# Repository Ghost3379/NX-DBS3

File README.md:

# NX-Edge

> **High-Density Modular Embedded Development Platform**  
> *M.2 2280 Key B • 6-Layer High-Density RF/Power Stackup • ESP32-S3 Dual-Core 240MHz • Autonomous LiPo Power-Path & Fuel Gauge • Dual-Antenna RF Front-End • Switched NeoPixel Driver*

---

<p align="center">
  <em>NX-Edge 3D Render — Dense 6-layer layout in M.2 2280 Key B form factor featuring 45° ESP32-S3, WSON-8 Flash, Ignion Chip Antenna + U.FL, LiPo Charger, Fuel Gauge, 2A Buck Regulator, and Switched NeoPixel Bus.</em>
</p>

---

## Overview

The **NX-Edge** is an ultra-dense, agile embedded development platform engineered to bridge the gap between high-speed benchtop prototyping and space-constrained, high-vibration interactive builds (tactical gear, robotics, custom sabers, wearable tech, and modular IoT nodes).

Built in the standard **M.2 2280 ($22 \times 80\text{ mm}$)** envelope on an advanced **6-layer high-density PCB** with **100% single-sided component placement** (zero components on the bottom layer), the NX-Edge delivers a **hybrid mechanical and electrical architecture**:

1. **The Modular Cartridge:** Standard **M.2 Key B edge connector** (up to 75 pins) allowing the board to slide directly into low-profile carrier boards, custom backplanes, or modular hilt sleds.
2. **The Castellated Prototyping Companion:** Dual perimeter rows of **castellated edge holes and solder pads** allow the board to be used directly on breadboards with pin headers, wired via fly-leads, or soldered flat as a surface-mount System-on-Module (SoM) onto carrier PCBs without requiring an M.2 socket.
3. **Zero-Z Flat Bottom:** Because all active ICs, passives, and connectors are strictly top-mounted, the bottom is flat copper and solder mask—allowing it to be mounted flush against aluminum chassis, heatsinks, 3D prints, or battery packs using thermal tape without risk of short circuits.

> [!IMPORTANT]
> **NX Custom Maker Interconnect (Non-PC Hardware):**  
> While the board utilizes the standard mechanical **M.2 Key B form factor and connector**, the pinout is a **custom, high-power maker standard** (similar to SparkFun MicroMod). The M.2 connector routes raw battery power, high-current 5V rails, speaker outputs, and 3.3V GPIOs directly to custom carrier boards. **Do NOT plug this board into a standard PC motherboard M.2 NVMe/SATA slot.**

---

## Current Hardware Implementation Status

| Subsystem / Block | Status | Key Components & Implementation Details |
| :--- | :---: | :--- |
| **Compute Core** | **Routed** | ESP32-S3 (bare QFN-56 @ 45°), 40 MHz 2016 crystal with symmetrical wings, decoupling network on power rails. |
| **Flash Memory** | **Routed** | 16 MB Winbond `W25Q128JVPIQ` (WSON-8), inline decoupling, Quad-SPI bus routed on internal Layer 3 stripline. |
| **RF Front-End** | **Routed** | Ignion `NN02-201` ceramic antenna + Hirose U.FL receptacle + Infineon `BGS12WN6` SPDT RF switch (`RF_CTRL`). |
| **USB Type-C** | **Routed** | Reversible Type-C receptacle, `USBLC6-2SC6` ESD array, dual $5.1\,\text{k}\Omega$ CC pulldowns (`R20`/`R21`), D+/D- internal stripline. |
| **LiPo Charging** | **Routed** | TI `BQ25170` autonomous linear charger (600–800 mA), status LED, horizontal JST-PH 2.0mm connector (`P1`/`P2`). |
| **True 0µA Standby** | **Routed** | Solder jumper & switch pad `JP2` between battery and system rail for an external physical power switch. |
| **Buck Regulator** | **Routed** | TI `TLV62569` synchronous buck converter delivering continuous **3.3V @ 2.0A** with low ripple. |
| **Fuel Gauge** | **Routed** | Maxim `MAX17048` ModelGauge™ I2C fuel gauge (`0x36`) for cell voltage ($V_{CELL}$) and SoC% without IR drop. |
| **NeoPixel Driver** | **Routed** | P-FET `Q2` (DMP3130L-7) + NPN `Q3` (BC847W) on `IO12` with 3 castellated pads (`VN`, `NPD_IN`, `GND`) for high-power strips. |
| **Onboard Indicators**| **Routed** | Onboard RGB NeoPixel (WS2812B/SK6812) powered from `VN` + User LED (LED13 / `D3`) with resistor `R13`. |
| **6-Layer Stackup** | **Configured**| Upgraded from 4-layer to high-density 6-layer with 0.45 mm / 0.25 mm micro-vias for optimal signal integrity. |
| **MicroSD Slot** | *Planned* | Molex 105162 push-pull slot running in native **4-bit hardware SDMMC** mode via ESP32-S3 DMA engine. |
| **Motion Sensor** | *Planned* | CEVA / Hillcrest Labs `BNO085` 9-DOF IMU with dedicated 32.768 kHz quartz crystal and sensor-fusion engine. |
| **Audio Amplifier** | *Planned* | Maxim `MAX98357A` I2S Class-D mono amplifier delivering up to 3.2W into 4Ω directly from `VIN`. |
| **RTC Subsystem** | *Planned* | Micro Crystal `RV-3028-C7` extreme low-power ($45\,\text{nA}$) real-time clock with backup cap `C34`. |

---

## 6-Layer High-Density Stackup Architecture

To ensure pristine signal integrity, zero electromagnetic interference (EMI) between the 2.4 GHz RF stage and high-speed digital buses, and effortless escape routing for QFN/WSON packages, the NX-Edge employs an industrial **6-layer symmetrical stackup**:

| Layer | KiCad Layer | Type | Copper Role & Signal Integrity Function |
| :---: | :---: | :---: | :--- |
| **L1** | `F.Cu` | Mixed / Top | Component mounting, 2.4 GHz RF transmission line, localized power pours (`VIN`, `+3V3`, `VBAT`). |
| **L2** | `In1.Cu` | Plane | **Solid Ground Plane (GND):** Uninterrupted return path and Faraday shield directly below Top layer. |
| **L3** | `In2.Cu` | Stripline Sig | **High-Speed Signal Highway:** Fully shielded internal striplines for **USB D+/D-**, **Flash Quad-SPI**, and **SDMMC**. |
| **L4** | `In3.Cu` | Power Plane | **Power Plane Mosaic:** Low-impedance internal distribution for `+3V3`, `VBUS`, and `VBAT`. |
| **L5** | `In4.Cu` | Plane | **Secondary Solid Ground Plane (GND):** Complete ground shield referencing Bottom layer. |
| **L6** | `B.Cu` | Mixed / Bottom | Non-critical escape routing, switched `VN` power plane, M.2 docking fingers, and edge test pads. |

* **Via Geometry:** Optimized to **0.45 mm pad diameter / 0.25 mm drill hole** (0.1 mm annular ring), shrinking via area by ~45% compared to standard 0.6/0.3 mm vias and allowing traces to slip between pins without DRC bottlenecks.

---

## Power Architecture & Power-Path Topology

The NX-Edge implements an autonomous, low-loss **Power-Path management architecture**:

```text
  USB-C (VBUS 5V) ──► [Schottky D2] ─────────┐
                                              │
  LiPo (VBAT) ────► [Hard-Cut JP2] ──► [Q1] ──┴─► [ VIN ] (Automatic System Rail)
                                        ▲           │
                                        │ Gate      ├─► [TLV62569 Buck] ──► +3V3 (2.0A)
                                  (VBUS Controlled) │
                                                    ├─► [MAX17048 Gauge] (I2C SoC Monitoring)
                                                    │
                                                    └─► [Q2 P-FET / Q3 NPN] ──► VN (Switched NeoPixel Rail)
                                                              ▲
                                                              │ GPIO12 (CTRL_NP)
```

1. **Automatic Power-Path Node (`VIN`):**
   * Sourced through Schottky diode from USB `VBUS` ($5.0\text{V}$) or low-loss P-MOSFET from battery `VBAT` ($3.7\text{–}4.2\text{V}$).
   * **USB Connected:** `VBUS` holds the P-FET gate high, completely isolating the battery from system discharge. `VIN` runs directly on USB power ($\approx 4.8\text{–}5.0\text{V}$).
   * **Battery Only:** When USB is disconnected, a gate pull-down immediately engages the P-FET ($R_{DS(on)} \approx 30\text{ m}\Omega$), supplying `VIN` with virtually zero voltage drop.
2. **System Buck Regulator (`TLV62569`):**
   * Synchronous step-down buck converter delivering **$3.3\text{V} @ \mathbf{2.0\text{A}}$ continuous** with $>95\%$ efficiency.
   * Powers the ESP32-S3, Flash, sensors, and peripherals cleanly without thermal throttling.
3. **Autonomous LiPo Charger (`BQ25170`):**
   * Standalone linear charger powered from `VBUS` configured for $600\text{–}800\text{ mA}$ charging with NTC thermistor input.
   * **Decoupled Charging:** Because the system and external LEDs run from `VIN`, charging current is never hijacked by system load.
4. **ModelGauge™ Fuel Gauge (`MAX17048`):**
   * Precision I2C fuel gauge (`0x36`) monitoring cell voltage directly at the battery connector. Reports cell voltage ($V_{CELL}$ in mV), State of Charge (SOC %), and rate of change over I2C without burning ADC channels or suffering from trace IR-drop.
5. **Smart NeoPixel Power-Cut (`VN`):**
   * High-side P-MOSFET `Q2` driven by NPN BJT `Q3` controlled via **GPIO12 (`CTRL_NP`)**.
   * In Standby/Deep Sleep (`CTRL_NP = LOW`), power to both onboard and external NeoPixels is cut to $0.0\text{V}$, eliminating the $\sim 1\text{ mA}$ per-pixel quiescent vampire draw ($0.0\,\mu\text{A}$ standby).

---

## RF Agility & Dual-Antenna Switching

* **RF Switch:** Infineon **`BGS12WN6`** ultra-miniature ($0.7 \times 1.1\text{ mm}$) SPDT RF switch rated up to $6\text{ GHz}$ with $<0.3\text{ dB}$ insertion loss.
* **Control:** Controlled via **`RF_CTRL`**:
  * **Low (Default):** On-board high-efficiency **Ignion NN02-201** ceramic chip antenna.
  * **High:** Micro-coaxial **Hirose U.FL / IPEX** receptacle for external antenna routing out of metal, carbon fiber, or shielded enclosures.

---

## Mechanical Specifications

* **Form Factor Standard:** M.2 2280 ($22.0\text{ mm} \times 80.0\text{ mm}$).
* **Connector Type:** M.2 Key B card edge (up to 75 pins).
* **PCB Thickness:** Standard $1.6\text{ mm}$ (or $0.8\text{ mm}$ option for slimline M.2 sockets).
* **Component Clearance:** 100% single-sided top placement. Completely flat bottom surface.
* **Prototyping Headers:** Dual-edge castellated pin holes for breadboards and surface mounting.

---

## License & Ownership

* **Hardware Design:** Licensed under the [CERN Open Hardware Licence Version 2 - Strongly Reciprocal (CERN-OHL-S)](https://ohwr.org/cernohl).
* **Firmware / BSP:** Licensed under the [GNU General Public License v3.0 (GPLv3)](https://www.gnu.org/licenses/gpl-3.0.en.html).
* **Engineering & Ownership:** Conceptualized, engineered, and maintained by [@Ghost3379](https://github.com/Ghost3379).

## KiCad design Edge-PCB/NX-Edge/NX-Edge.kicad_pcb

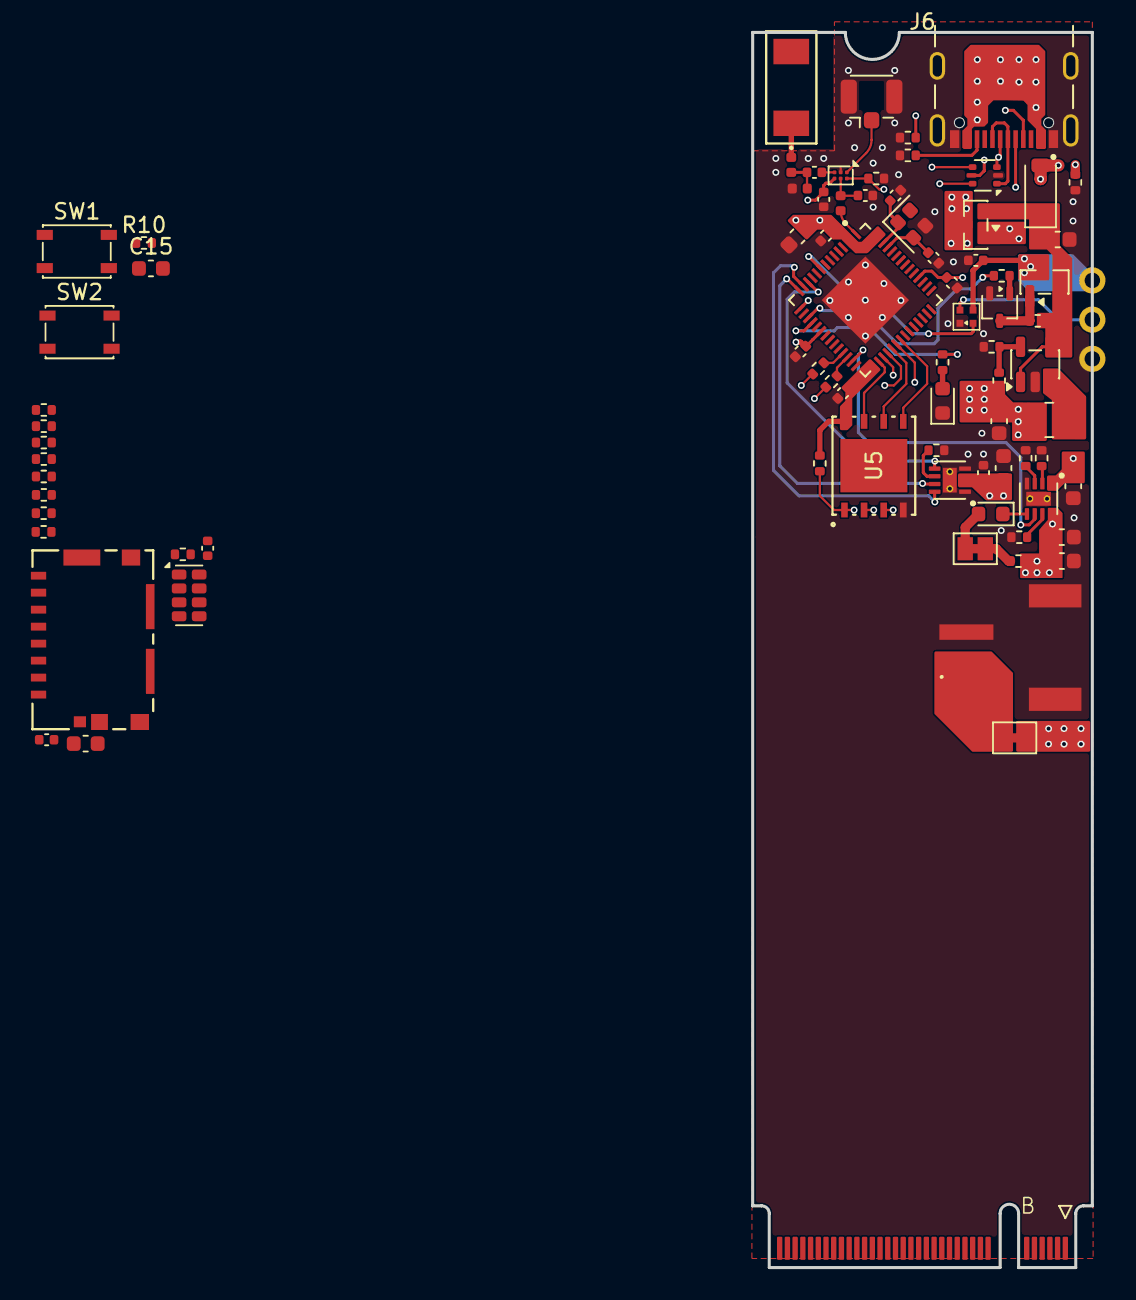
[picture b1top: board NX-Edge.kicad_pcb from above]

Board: 6 copper layers, 22.0 x 80.0 mm, 80 parts (0 on the bottom side), 64 nets.

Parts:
AE1: NN02-201; ANT_NN02-201_IGN
AE2: U-FL Connector; U.FL_Hirose_U.FL-R-SMT-1_Vertical
C1, C2, C15, C22: 1u; C_0603_1608Metric
C3, C5, C7, C20: 10u; C_0603_1608Metric
C4: 4.7u; C_0603_1608Metric
C6, C8, C11, C12, C16, C19, C21, C23, C24: 100n; C_0402_1005Metric
C13, C14: TBA; C_0402_1005Metric
C17, C18: 12p; C_0402_1005Metric
D1: ORANGE; LED_0603_1608Metric
D2: NRVB230LSFT1G; D_SOD-123
D3: BLUE; LED_0603_1608Metric
J1: 1051620001; 105162-0001_MOL
J3: UJ20-C-H-G-SMT-1-P16-TR; SAMESKY_UJ20-C-H-G-SMT-1-P16-TR
J6: Bus_M.2_Socket_B; M.2_2280-xx-B
J7: Ext. NeoPixel; PinHeader_1x03_P2.54mm_Vertical
JP1: CUT2DISABLE; SolderJumper-2_P1.3mm_Bridged_Pad1.0x1.5mm
JP2: PLACE4SWITCH; SolderJumper-2_P1.3mm_Bridged_Pad1.0x1.5mm
L1: 1u; L_1008_2520Metric
L2, L3, L4: TBA; L_0402_1005Metric
P1: S2B-PH-SM4-TB; JST_S2B-PH-SM4-TB
Q1, Q2: DMP3130L-7; SOT-23
Q3: BC847W; SOT-323_SC-70
R1, R8, R13: 1k; R_0402_1005Metric
R2: 27k; R_0402_1005Metric
R3: 499; R_0402_1005Metric
R4: 453k; R_0402_1005Metric
R5, R6, R9, R11: 100k; R_0402_1005Metric
R7, R14: 10k; R_0402_1005Metric
R10: 10K; R_0402_1005Metric
R12: 100K; R_0402_1005Metric
R20, R21: 5.1k; R_0402_1005Metric
R23, R28, R29, R30, R31, R32, R33, R34: 4k7; R_0402_1005Metric
R24, R27: 22; R_0402_1005Metric
SW1: RST; SW_SPST_PTS810
SW2: BOOT; SW_SPST_PTS810
TH1: 10k NTC; R_0402_1005Metric
U1: BQ25170DSGR; SON50P200X200X80-9N
U2: TLV62569DBV; SOT-23-5
U3: BGS12WN6E6327; Infineon_PG-TSNP-6-10_0.7x1.1mm_0.7x1.1mm_P0.4mm
U4: ESP32-S3R8; QFN40P700X700X90-57N
U5: W25Q128JVPIQ; WSON_128JVPIQ_WIN
U6: MAX17048G_T10; SON50P200X200X80-9N
U7: RV-3028-C7; MicroCrystal_C7_SON-8_1.5x3.2mm_P0.9mm
U8: XL-1010RGBC-WS2812B; LED-SMD_4P-L1.0-W1.0-TL_XL-1010RGBC-WS2812B
U11: USBLC6-2P6; SOT-666
Y1: 40MHz; Crystal_SMD_2016-4Pin_2.0x1.6mm

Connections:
+3V3: C5.1, C6.1, C7.1, C8.1, C11.1, C12.1, C19.1, C20.1, C23.1, J1.P4 (VDD), L1.2, R4.2, R10.2, R23.1, R28.1, R29.1, R30.1, R31.1, R32.1, R33.1, R34.1, U3.4 (VDD), U4.2 (VDD3P3), U4.3 (VDD3P3), U4.20 (VDD3P3_RTC), U4.46 (VDD3P3_CPU), U4.55 (VDDA1), U4.56 (VDDA2), U7.7 (VDD)
/Connections/CC1: J3.A5 (CC1), R20.1
/Connections/CC2: J3.B5 (CC2), R21.1
/Connections/D+: R24.1, U11.6 (I/O1)
/Connections/D-: R27.1, U11.4 (I/O2)
/Connections/IO0: SW2.2, U4.5 (GPIO0)
/Connections/IO8: R28.2, U4.13 (GPIO8), U6.8 (SDA), U7.4 (SDA)
/Connections/IO9: R23.2, U4.14 (GPIO9), U6.7 (SCL), U7.3 (SCL)
/Connections/NPDE_IN: J7.2, U8.1 (DOUT)
/Connections/RST: C15.1, R10.1, SW1.2, U4.4 (CHIP_PU)
/Connections/U_D+: J3.A6 (DP1), J3.B6 (DP2), U11.1 (I/O1)
/Connections/U_D-: J3.A7 (DN1), J3.B7 (DN2), U11.3 (I/O2)
/Logic section/CTRL_RF: R9.2, U3.6 (CTRL), U4.15 (GPIO10)
/Logic section/IO2: J1.P2 (CD/DAT3), R33.2, U4.7 (GPIO2)
/Logic section/IO4: U4.9 (GPIO4), U8.4 (DIN)
/Logic section/IO5: R34.2, U4.10 (GPIO5)
/Logic section/IO6: U4.11 (GPIO6), U7.2 (~INT)
/Logic section/IO7: U4.12 (GPIO7), U6.5 (~ALERT)
/Logic section/IO12: R8.2, U4.17 (GPIO12)
/Logic section/IO13: R13.1, U4.18 (GPIO13)
/Logic section/IO21: U1.6 (~PG), U4.27 (GPIO21)
/Logic section/IO38: J1.P3 (CMD), R29.2, U4.43 (GPIO38)
/Logic section/MTCK: J1.P5 (CLK), U4.44 (MTCK)
/Logic section/MTDI: J1.P8 (DAT1), R31.2, U4.47 (MTDI)
/Logic section/MTDO: J1.P7 (DAT0), R30.2, U4.45 (MTDO)
/Logic section/MTMS: J1.P1 (DAT2), R32.2, U4.48 (MTMS)
/Logic section/SPICLK: U4.33 (SPICLK), U5.6 (CLK)
/Logic section/SPICS0: R11.1, U4.32 (SPICS0), U5.1 (!CS)
/Logic section/SPID: U4.35 (SPID), U5.5 (DI_(IO0))
/Logic section/SPIHD: U4.30 (SPIHD), U5.7 (!HOLD(IO3))
/Logic section/SPIQ: U4.34 (SPIQ), U5.2 (DO_(IO1))
/Logic section/SPIWP: U4.31 (SPIWP), U5.3 (!WP_(IO2))
GND: AE2.2 (Ext), C1.2, C2.2, C3.2, C4.2, C5.2, C6.2, C7.2, C8.2, C11.2, C12.2, C14.2, C15.2, C16.2, C17.2, C18.2, C19.2, C20.2, C21.2, C22.2, C23.2, C24.2, D3.1 (K), J1.G1 (GND_2), J1.G2 (GND_3), J1.G3 (GND_4), J1.G4 (GND), J1.P6 (VSS), J3.A1_B12 (GND), J3.B1_A12 (GND__1), J3.SH1 (SHIELD), J3.SH2 (SHIELD__1), J3.SH3 (SHIELD__2), J3.SH4 (SHIELD__3), J7.1, L3.1, P1.2, P1.3, P1.4, Q3.2 (E), R2.1, R3.1, R5.1, R6.1, R9.1, R12.1, R14.1, R20.2, R21.2, SW1.1, SW2.1, TH1.2, U1.4 (GND), U1.9 (EXP), U2.2 (GND), U3.2 (GND), U4.57 (GND), U5.4 (GND), U6.1 (CTG), U6.4 (GND), U6.9 (EP), U7.5 (VSS), U8.3 (GND), U11.2 (GND), Y1.3
unnamed: AE1.1 (1_1), L2.2
unnamed: AE2.1 (In), U3.1 (RF2)
unnamed: C13.1, L2.1, L3.2
unnamed: D1.2 (A), JP1.2 (B)
unnamed: D1.1 (K), U1.5 (STAT)
unnamed: D3.2 (A), R13.2
unnamed: J6.2 (3.3V), J6.4 (3.3V), J6.70 (3.3V), J6.72 (3.3V), J6.74 (3.3V)
unnamed: J6.3 (GND), J6.5 (GND), J6.11 (GND), J6.27 (GND), J6.33 (GND), J6.39 (GND), J6.45 (GND), J6.51 (GND), J6.57 (GND), J6.71 (GND), J6.73 (GND)
unnamed: JP1.1 (A), R1.2
unnamed: JP2.2 (B), P1.1
unnamed: Q2.1 (G), Q3.3 (C), R7.1
unnamed: Q3.1 (B), R8.1
unnamed: R3.2, U1.2 (ISET)
unnamed: TH1.1, U1.3 (TS)
unnamed: R2.2, U1.7 (VSET)
unnamed: R4.1, R6.2, U2.5 (FB)
unnamed: L1.1, U2.3 (SW)
unnamed: C13.2, U3.3 (RF1)
unnamed: C14.1, L4.1, U3.5 (RFIN)
unnamed: L4.2, U4.1 (LNA_IN)
unnamed: R24.2, U4.26 (USB_D+(GPIO_20))
unnamed: R27.2, U4.25 (USB_D-(GPIO_19))
unnamed: C18.1, U4.53 (XTAL_N), Y1.2
unnamed: C17.1, U4.54 (XTAL_P), Y1.1
unnamed: R12.2, U6.6 (QSTRT)
unnamed: R14.2, U7.8 (EVI)
VBAT: C2.1, C3.1, C21.1, C22.1, JP2.1 (A), Q1.3 (D), R1.1, U1.8 (OUT), U6.2 (CELL), U6.3 (VDD)
VBUS: C1.1, D2.2 (A), J3.A4_B9 (VBUS), J3.B4_A9 (VBUS__1), Q1.1 (G), R5.2, U1.1 (IN), U11.5 (VBUS)
VDD_SPI: C16.1, R11.2, U4.29 (VDD_SPI), U5.8 (VCC)
VIN: C4.1, D2.1 (K), Q1.2 (S), Q2.2 (S), R7.2, U2.1 (EN), U2.4 (VIN)
VN: C24.1, J7.3, Q2.3 (D), U8.2 (VDD)

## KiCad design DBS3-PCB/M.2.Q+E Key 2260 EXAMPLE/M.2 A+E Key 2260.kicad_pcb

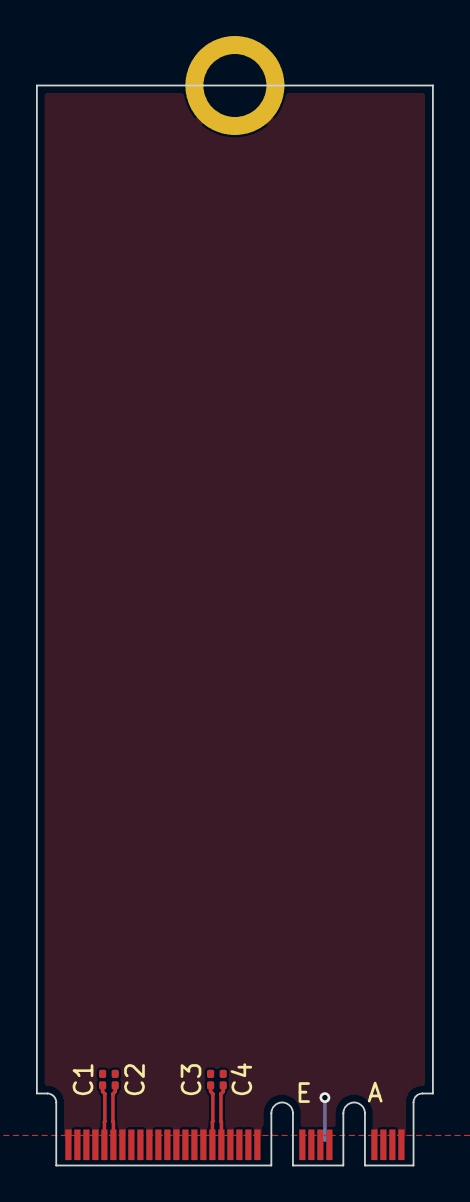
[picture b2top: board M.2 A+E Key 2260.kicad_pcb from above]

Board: 2 copper layers, 22.0 x 60.0 mm, 6 parts (0 on the bottom side), 6 nets.

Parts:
C1, C2, C3, C4: 220nF; C_0201_0603Metric
H1: MountingHole_Pad; M.2 Mounting Pad
J1: M.2 A+E Key Connector

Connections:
+3.3V: J1.2 (+3.3V), J1.4 (+3.3V), J1.72 (+3.3V), J1.74 (+3.3V)
/M.2 A+E Key/PET0N: C3.1, J1.43 (PETn0)
/M.2 A+E Key/PET0P: C4.1, J1.41 (PETp0)
/M.2 A+E Key/PET1N: C1.1, J1.67 (RESERVED/PETn1)
/M.2 A+E Key/PET1P: C2.1, J1.65 (RESERVED/PETp1)
GND: H1.1, J1.1 (GND), J1.7 (GND), J1.18 (GND), J1.33 (GND), J1.39 (GND), J1.45 (GND), J1.51 (GND), J1.57 (GND), J1.63 (GND), J1.69 (GND), J1.75 (GND)
